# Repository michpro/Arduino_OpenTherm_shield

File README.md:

# **Arduino UNO OpenTherm Shield**

- [**Arduino UNO OpenTherm Shield**](#arduino-uno-opentherm-shield)
  - [**Overview**](#overview)
    - [**Features**](#features)
  - [**Schematic diagram**](#schematic-diagram)
  - [**Module visualisation**](#module-visualisation)
  - [**Assembly**](#assembly)
  - [**Production files**](#production-files)
  - [**Testing out the hardware**](#testing-out-the-hardware)
    - [Prerequisites](#prerequisites)
    - [Instructions](#instructions)
    - [Notes](#notes)
  - [**Software**](#software)
  - [**Reporting bugs**](#reporting-bugs)
  - [**License**](#license)
    - [**Hardware**](#hardware)
    - [**Software**](#software-1)
  - [**Support**](#support)

---

## **Overview**
The Arduino OpenTherm Shield is an open-source hardware interface designed to enable an Arduino microcontroller to communicate with heating systems using the OpenTherm protocol.
OpenTherm is a point-to-point communication protocol commonly used in modern heating systems for efficient control and monitoring.
This shield provides the necessary voltage conversion, electrical isolation, and signal conditioning to interface the Arduinos 5V or 3.3V logic
with the OpenTherm bus, which typically operates at higher voltages (24V).

  ### **Features**
  * OpenTherm slave interface to communicate with a boiler
  * OpenTherm master interface to communicate with a thermostat
  * can implement master, slave and gateway modes
  * built-in (3.3-5V) to 24V DC-DC step up converter
  * Arduino UNO compatible shield

This work is based on [otgw.tclcode.com](https://otgw.tclcode.com) project.

---

## **Schematic diagram**

## **Module visualisation**
(click on the image to see the 3D model)
<p align="center"></p>

## **Assembly**
[Interactive BOM and placement](https://michpro.github.io/Arduino_OpenTherm_shield/ibom.html)

For Arduino UNO:
* JP1 jumper – leave in the Auto position (V<sub>cc</sub> from IOREF).

For WeMos D1 UNO:
* JP1 jumper - this board is not fully compatible with Arduino specifications - the IOREF pin on this board should have a voltage of 3.3V, but it has 5V. Therefore, cut the default jumper between the Auto and V<sub>cc</sub> pads and use a drop of tin to connect the V<sub>cc</sub> pad to 3.3V.<br>*You can also modify the WeMos D1 UNO so that the IOREF pin has the correct voltage of 3.3V*.

Other boards:
* This shield should also be compatible with other boards. You only need to check the correct voltage on the IOREF pin (and possibly make a change as for WeMos D1 UNO) and, if necessary, adjust the software to the board definition.

## **Production files**
Production files can be found [**here**](./production/).

---

## **Testing out the hardware**
Below are the start-up instructions for the ["shield_test.ino"](./software/shield_test/shield_test.ino) Arduino program, a diagnostic tool designed to test and validate the electrical and communication integrity between a boiler and thermostat circuits on the OpenTherm shield. These instructions guide you through the process step-by-step, ensuring you can verify your hardware setup correctly.

### Prerequisites
- **Arduino Board**: Use an AVR family board (e.g., Arduino UNO).
- **OpenTherm Shield**: Ensure it is properly connected to the Arduino.
- **Computer**: Equipped with Arduino IDE or a serial monitor software.
- **Multimeter**: Required for measuring voltages and currents.
- **Two Wires**: Needed to connect the BOILER and THERM terminals during testing.

### Instructions

1. **Upload the Program**
   - Load the ["shield_test.ino"](./software/shield_test/shield_test.ino) program onto your Arduino board (Arduino UNO preffered) using the Arduino IDE.<br>
    *If necessary, adjust the pins used in the programme.*

2. **Open Serial Monitor**
   - Launch the serial monitor in the Arduino IDE or your preferred serial terminal software.
   - Set the baud rate to **115200**.

3. **Initial Setup**
   - Disconnect the 'THERM' and 'BOILER' terminals from each other if they are connected.
   - Check the LEDs on the shield:
     - **'PWR'** and **'RxT'** LEDs should be lit.
     - **'RxB'** LED should be off.
   - The serial monitor will display a prompt. If the LED statuses match, type **`y`** and press Enter to proceed.

4. **Voltage Measurement 1**
   - Use a multimeter to measure the voltage between the **+24V test point** and **GND**.
   - Expected range: **23.5V to 24.5V**.
   - If within range, type **`y`** in the serial monitor to proceed.

5. **Voltage Measurement 2**
   - Measure the voltage between the **T+ test point** and **GND**.
   - Expected value: Approximately **24V**.
   - If correct, type **`y`** to proceed.

6. **Current Measurement 1**
   - Measure the current flowing between **T+** and **GND**.
   - Expected range: **5mA to 9mA**.
   - Verify that the **RxT LED** is **not lit** during this measurement.
   - If correct, type **`y`** to proceed.

7. **Activate MASTER-OUT and Current Measurement 2**
   - The program will activate the 'MASTER-OUT' line (you’ll see a message in the serial monitor).
   - Measure the current between **T+** and **GND** again.
   - Expected range: **17mA to 23mA**.
   - Ensure the **RxT LED** remains **not lit**.
   - If correct, type **`y`** to proceed.

8. **Connect Terminals and Voltage Measurement 3**
   - Connect the **BOILER** and **THERM** terminals using two wires (polarity does not matter).
   - Measure the voltage between test points **B1** and **B2**.
   - Expected range: **15V to 18V**.
   - If within range, type **`y`** to proceed.

9. **Check RxB LED**
   - The program will activate 'MASTER-OUT' again.
   - Observe the **'RxB' LED**; it should **light up**.
   - If it does, type **`y`** to proceed.

10. **Activate SLAVE-OUT and Voltage Measurement 4**
    - The program will activate the 'SLAVE-OUT' line.
    - Check that the **RxT LED** **stops lighting up**.
    - Measure the voltage between **B1** and **B2** again.
    - Expected range: **5V to 7V**.
    - If correct, type **`y`** to proceed.

11. **Test Result**
    - If all steps are completed successfully, the serial monitor will display:
      ```
      *****************
      *  TEST PASSED  *
      *****************
      ```
    - If any step fails, it will show:
      ```
      *****************
      * TEST FAIL !!! *
      *****************
      ```

12. **Continuous Testing (if passed)**
    - If the test passes, the program will enter a continuous testing mode.
    - It will repeatedly check communication between the boiler and thermostat, printing:
      - **"Boiler inbound, thermostat outbound ... OK"** or **"Failed"** with a reason.
      - **"Boiler outbound, thermostat inbound ... OK"** or **"Failed"** with a reason.

### Notes
- **Test Points and LEDs**: Ensure you correctly identify the test points (+24V, T+, GND, B1, B2) and LEDs (PWR, RxT, RxB) on the OpenTherm shield.
- **Safety**: Exercise caution when measuring voltages and currents to avoid short circuits.
- **Troubleshooting**: If a measurement falls outside the expected range:
  - Double-check your connections and multimeter settings.
  - Retry the step. Persistent issues may indicate a problem with the shield or setup.

<br>

***Follow these instructions carefully to test and validate your OpenTherm shield setup. Each step requires confirmation via the serial monitor, so keep it open and active throughout the process. Successful completion ensures your boiler and thermostat circuits are functioning correctly.***

---

## **Software**
- Recommended library for use in your OpenTherm projects: 
  [https://github.com/ihormelnyk/opentherm_library](https://github.com/ihormelnyk/opentherm_library)

---

## **Reporting bugs**

[Create an issue on GitHub](https://github.com/michpro/Arduino_OpenTherm_shield/issues)

---

## **License**
Copyright © 2025 Michal Protasowicki

### **Hardware**
  * Hardware part of this project is released under CERN Open Hardware Licence Version 2 - Permissive.

### **Software**
  * Software part of this project is released under MIT Licence.

---

## **Support**
If You find my projects interesting and You wanted to support my work, You can give me a cup of coffee or a keg of beer :)

&nbsp;&nbsp;&nbsp;&nbsp;&nbsp;&nbsp;&nbsp;&nbsp;&nbsp;&nbsp;

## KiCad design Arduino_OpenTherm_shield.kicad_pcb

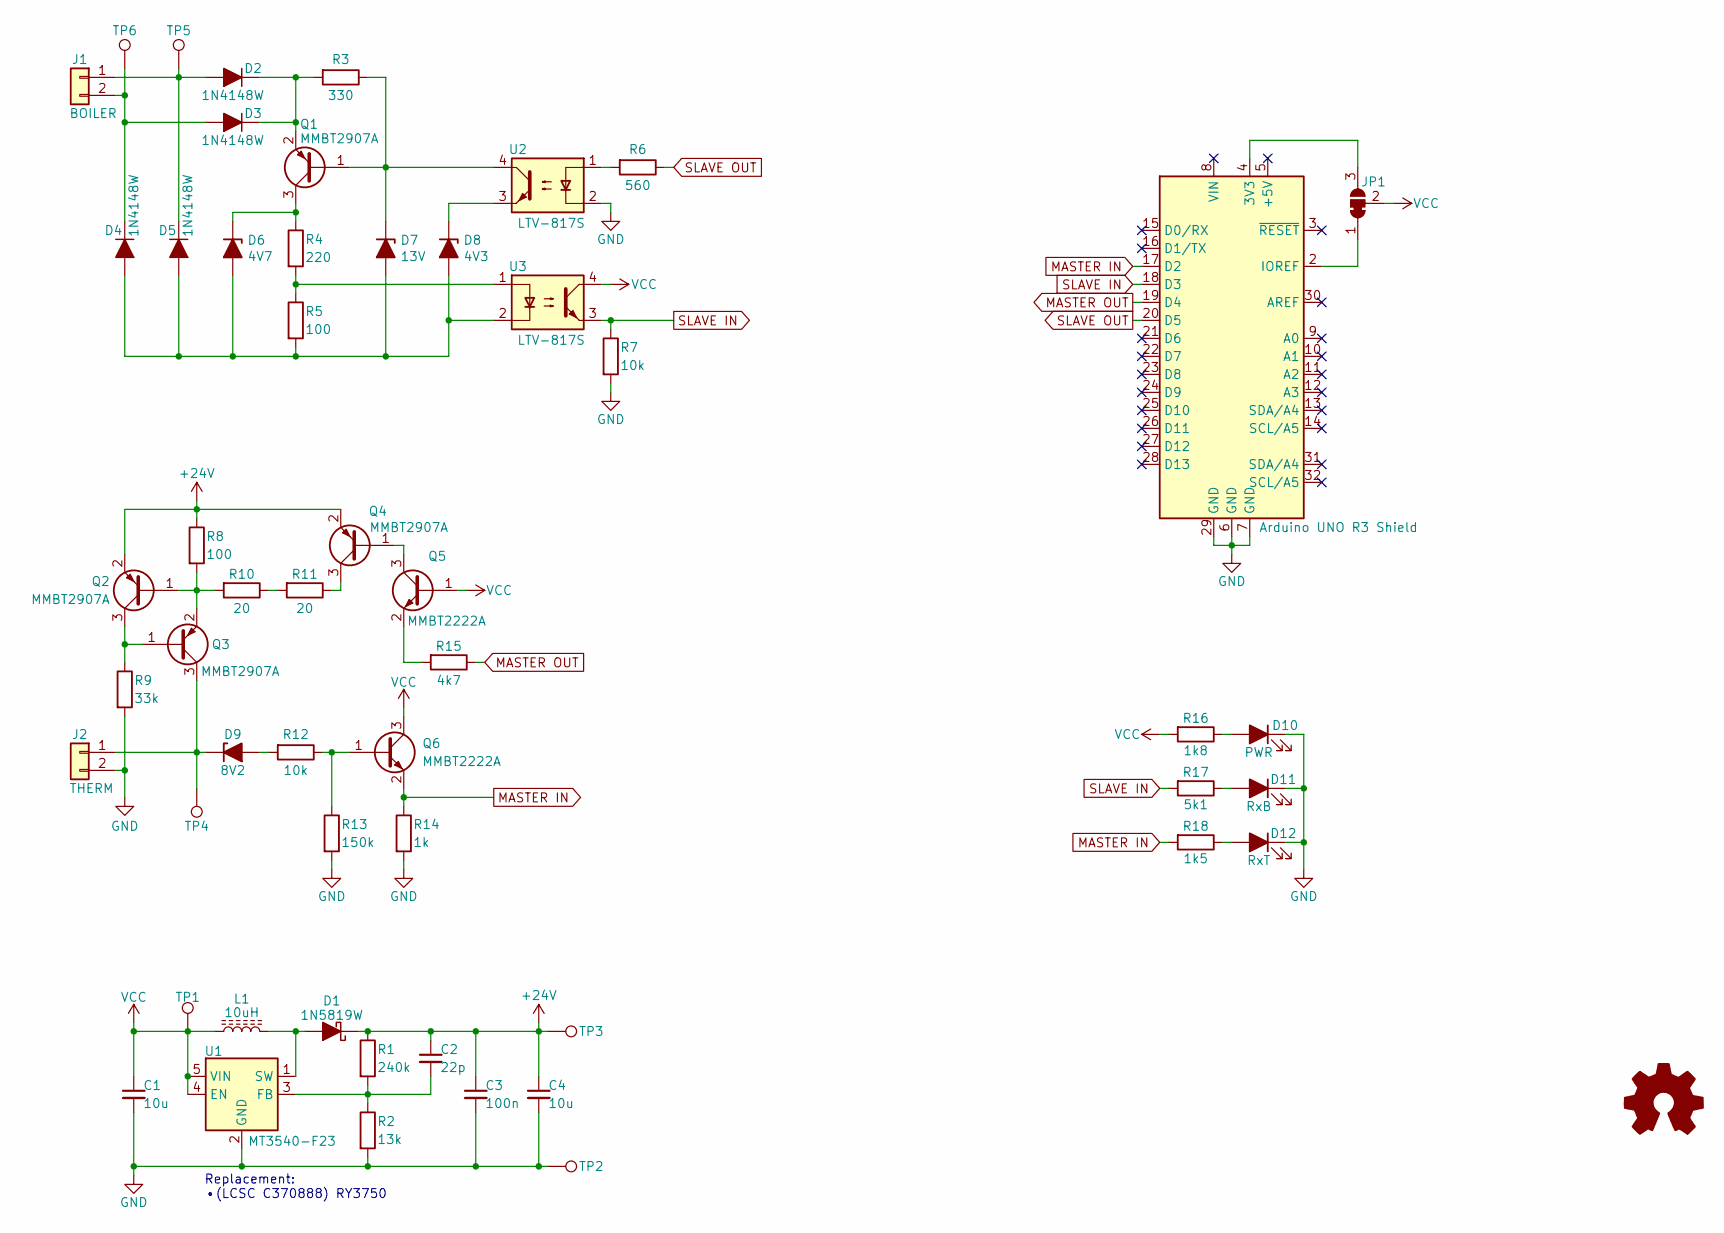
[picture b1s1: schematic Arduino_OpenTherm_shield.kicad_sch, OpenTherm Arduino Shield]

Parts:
A1: Arduino UNO R3 Shield; Arduino_UNO_R3_WithMountingHoles_Profiled; LCSC ------
C1: 10u; C_0603_1608Metric; LCSC C19702
C2: 22p; C_0603_1608Metric; LCSC C1653
C3: 100n; C_0603_1608Metric; LCSC C14663
C4: 10u; C_0805_2012Metric; LCSC C440198
D1: 1N5819W; D_SOD-123; LCSC C8598
D2, D3, D4, D5: 1N4148W; D_SOD-123; LCSC C7420318
D6: 4V7; D_SOD-123; LCSC C19077400
D7: 13V; D_SOD-123; LCSC C22399883
D8: 4V3; D_SOD-123; LCSC C19077399
D9: 8V2; D_SOD-123; LCSC C22399882
D10: PWR; LED_0805_2012Metric; LCSC C84256
D11: RxB; LED_0805_2012Metric; LCSC C2297
D12: RxT; LED_0805_2012Metric; LCSC C2296
J1: BOILER; Altech_AK100_1x02_P5.00mm; LCSC ------
J2: THERM; Altech_AK100_1x02_P5.00mm; LCSC ------
JP1: VCC; SolderJumper-3_P1.3mm_Bridged12_RoundedPad1.0x1.5mm; LCSC ------
L1: 10uH; Inductor_4.2x4.4mm; LCSC C177242
LOGO3: Logo_Open_Hardware_Small; OSHW-Logo2_7.3x6mm_SilkScreen
Q1, Q2, Q3, Q4: MMBT2907A; SOT-23; LCSC C7420352
Q5, Q6: MMBT2222A; SOT-23; LCSC C8512
R1: 240k; R_0603_1608Metric; LCSC C4197
R2: 13k; R_0603_1608Metric; LCSC C22797
R3: 330; R_0603_1608Metric; LCSC C23138
R4: 220; R_0603_1608Metric; LCSC C22962
R5, R8: 100; R_0603_1608Metric; LCSC C22775
R6: 560; R_0603_1608Metric; LCSC C23204
R7, R12: 10k; R_0603_1608Metric; LCSC C25804
R9: 33k; R_0603_1608Metric; LCSC C4216
R10, R11: 20; R_0603_1608Metric; LCSC C22950
R13: 150k; R_0603_1608Metric; LCSC C22807
R14: 1k; R_0603_1608Metric; LCSC C21190
R15: 4k7; R_0603_1608Metric; LCSC C23162
R16: 1k8; R_0603_1608Metric; LCSC C4177
R17: 5k1; R_0603_1608Metric; LCSC C23186
R18: 1k5; R_0603_1608Metric; LCSC C22843
TP1: VCC; TestPoint_Pad_D2.0mm; LCSC ------
TP2: GND; TestPoint_Pad_D2.0mm; LCSC ------
TP3: +24V; TestPoint_Pad_D2.0mm; LCSC ------
TP4: T+; TestPoint_Pad_D2.0mm; LCSC ------
TP5: B1; TestPoint_Pad_D2.0mm; LCSC ------
TP6: B2; TestPoint_Pad_D2.0mm; LCSC ------
U1: MT3540-F23; SOT-23-5; LCSC C181783
U2, U3: LTV-817S; SMDIP-4_W9.53mm; LCSC C109227

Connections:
+24V: C2.1, C3.1, C4.1, D1.1 (K), Q2.2 (E), Q4.2 (E), R1.1, R8.1, TP3.1
GND: A1.6 (GND), A1.7 (GND), A1.29 (GND), C1.2, C3.2, C4.2, D10.1 (K), D11.1 (K), D12.1 (K), J2.2, R2.2, R7.2, R9.2, R13.2, R14.2, TP2.1, U1.2 (GND), U2.2
MASTER IN: A1.17 (D2), Q6.2 (E), R14.1, R18.2
MASTER OUT: A1.19 (D4), R15.1
unnamed: A1.4 (3V3), JP1.3 (B)
unnamed: A1.2 (IOREF), JP1.1 (A)
unnamed: D1.2 (A), L1.2, U1.1 (SW)
unnamed: D2.2 (A), D5.1 (K), J1.1, TP5.1
unnamed: D2.1 (K), D3.1 (K), Q1.2 (E), R3.2
unnamed: D3.2 (A), D4.1 (K), J1.2, TP6.1
unnamed: D4.2 (A), D5.2 (A), D6.2 (A), D7.2 (A), D8.2 (A), R5.2, U3.2
unnamed: D6.1 (K), Q1.3 (C), R4.1
unnamed: D7.1 (K), Q1.1 (B), R3.1, U2.4
unnamed: D8.1 (K), U2.3
unnamed: D9.2 (A), R12.2
unnamed: D9.1 (K), J2.1, Q3.3 (C), TP4.1
unnamed: D10.2 (A), R16.1
unnamed: D11.2 (A), R17.1
unnamed: D12.2 (A), R18.1
unnamed: Q2.1 (B), Q3.2 (E), R8.2, R10.2
unnamed: Q2.3 (C), Q3.1 (B), R9.1
unnamed: Q4.1 (B), Q5.3 (C)
unnamed: Q4.3 (C), R11.1
unnamed: Q5.2 (E), R15.2
unnamed: Q6.1 (B), R12.1, R13.1
unnamed: R4.2, R5.1, U3.1
unnamed: R6.2, U2.1
unnamed: R10.1, R11.2
unnamed: C2.2, R1.2, R2.1, U1.3 (FB)
SLAVE IN: A1.18 (D3), R7.1, R17.2, U3.3
SLAVE OUT: A1.20 (D5), R6.1
VCC: C1.1, JP1.2 (C), L1.1, Q5.1 (B), Q6.3 (C), R16.2, TP1.1, U1.4 (EN), U1.5 (VIN), U3.4

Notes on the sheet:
Replacement: •(LCSC C370888) RY3750

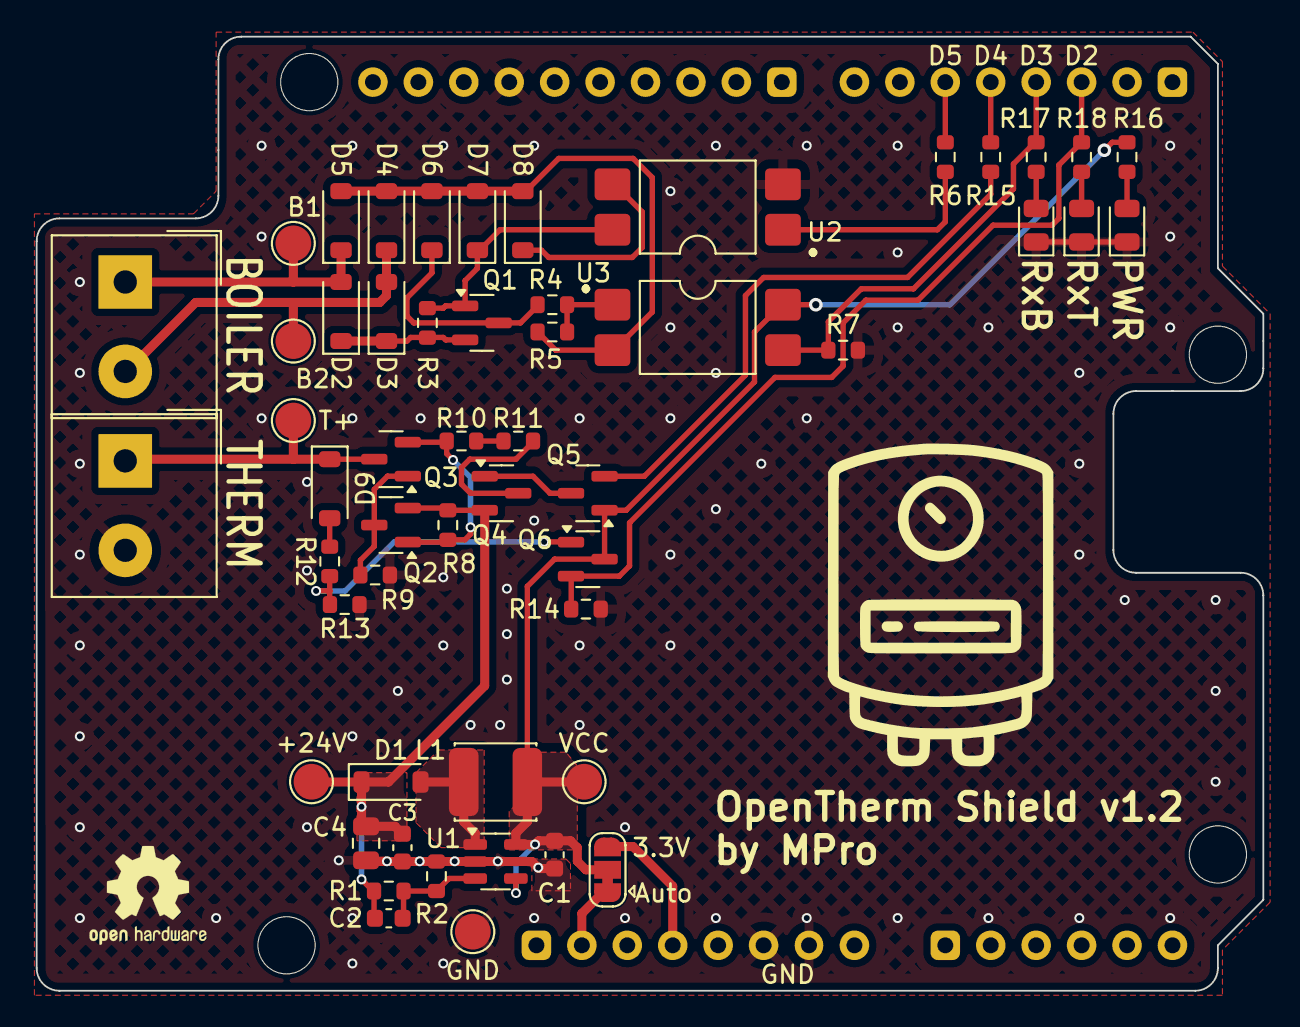
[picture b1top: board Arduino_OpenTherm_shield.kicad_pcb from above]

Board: 2 copper layers, 68.6 x 53.3 mm, 55 parts (0 on the bottom side), 32 nets.

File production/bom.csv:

Designator,Footprint,Quantity,Value,LCSC Part #
C1,0603,1,10u,C19702
C2,0603,1,22p,C1653
C3,0603,1,100n,C14663
C4,0805,1,10u,C440198
D1,D_SOD-123,1,1N5819W,C8598
D10,0805,1,PWR,C84256
D11,0805,1,RxB,C2297
D12,0805,1,RxT,C2296
"D2, D3, D4, D5",D_SOD-123,4,1N4148W,C7420318
D6,D_SOD-123,1,4V7,C19077400
D7,D_SOD-123,1,13V,C22399883
D8,D_SOD-123,1,4V3,C19077399
D9,D_SOD-123,1,8V2,C22399882
L1,Inductor_4.2x4.4mm,1,10uH,C177242
"Q1, Q2, Q3, Q4",SOT-23,4,MMBT2907A,C7420352
"Q5, Q6",SOT-23,2,MMBT2222A,C8512
R1,0603,1,240k,C4197
"R10, R11",0603,2,20,C22950
"R12, R7",0603,2,10k,C25804
R13,0603,1,150k,C22807
R14,0603,1,1k,C21190
R15,0603,1,4k7,C23162
R16,0603,1,1k8,C4177
R17,0603,1,5k1,C23186
R18,0603,1,1k5,C22843
R2,0603,1,13k,C22797
R3,0603,1,330,C23138
R4,0603,1,220,C22962
"R5, R8",0603,2,100,C22775
R6,0603,1,560,C23204
R9,0603,1,33k,C4216
U1,SOT-23-5,1,MT3540-F23,C181783
"U2, U3",SMDIP-4_W9.53mm,2,LTV-817S,C109227

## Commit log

2025-04-01 HW rev 1.1
2025-04-16 Corrected value of the resistance responsible for the High state of the OT bus
2025-04-24 updated bom list
2025-06-03 interactive OpenTherm shield testing program
2025-07-11 HW rev 1.2 [fixed translation of MASTER_IN signal logic levels]
2025-08-05 readme file added
2025-09-14 RxB LED brightness adjusted

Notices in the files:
Arduino_OpenTherm_shield.kicad_pcb:
© 2025 MPro
Licensed under CERN-OHL-P v2 or any later version
README.md:
License: CERN-OHL-P-2.0
License: MIT
